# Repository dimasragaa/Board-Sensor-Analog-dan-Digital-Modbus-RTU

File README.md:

# Board-Sensor-Analog-dan-Digital-Modbus-RTU

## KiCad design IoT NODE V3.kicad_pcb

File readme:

# PCB IoT Node - Tugas Akhir

## 📖 Deskripsi Proyek

Repositori ini berisi file desain perangkat keras (Schematic & PCB Layout) dan dokumentasi untuk **IoT Node**. Proyek ini dikembangkan sebagai bagian dari **Tugas Akhir** di Departemen Teknik Elektro, Institut Teknologi Sepuluh Nopember (ITS).

PCB ini dirancang untuk berfungsi sebagai node sensor/aktuator dalam sistem Internet of Things, dengan fokus pada efisiensi daya dan konektivitas yang handal.

## 👤 Penulis

**Dimas Raga**
*   **Institusi:** Teknik Elektro, Institut Teknologi Sepuluh Nopember (ITS)
*   **GitHub:** https://github.com/dimasraga
*   **Instagram:** https://www.instagram.com/dmsragaa

## 📄 Lisensi

Proyek ini dilisensikan di bawah lisensi MIT - lihat file LICENSE untuk detailnya.

---
*Dibuat untuk memenuhi persyaratan Tugas Akhir Teknik Elektro ITS.*

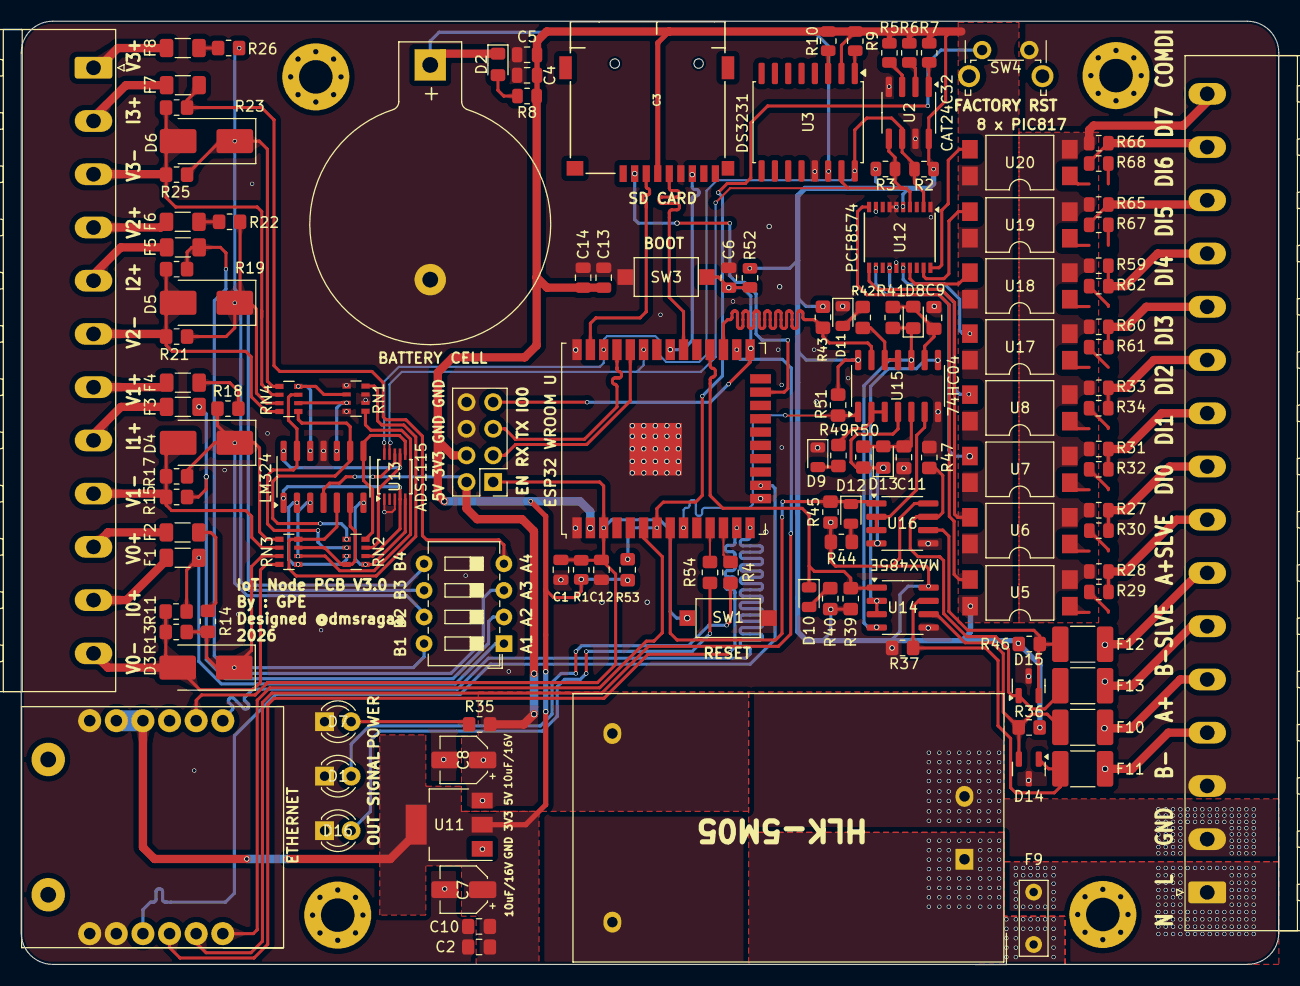
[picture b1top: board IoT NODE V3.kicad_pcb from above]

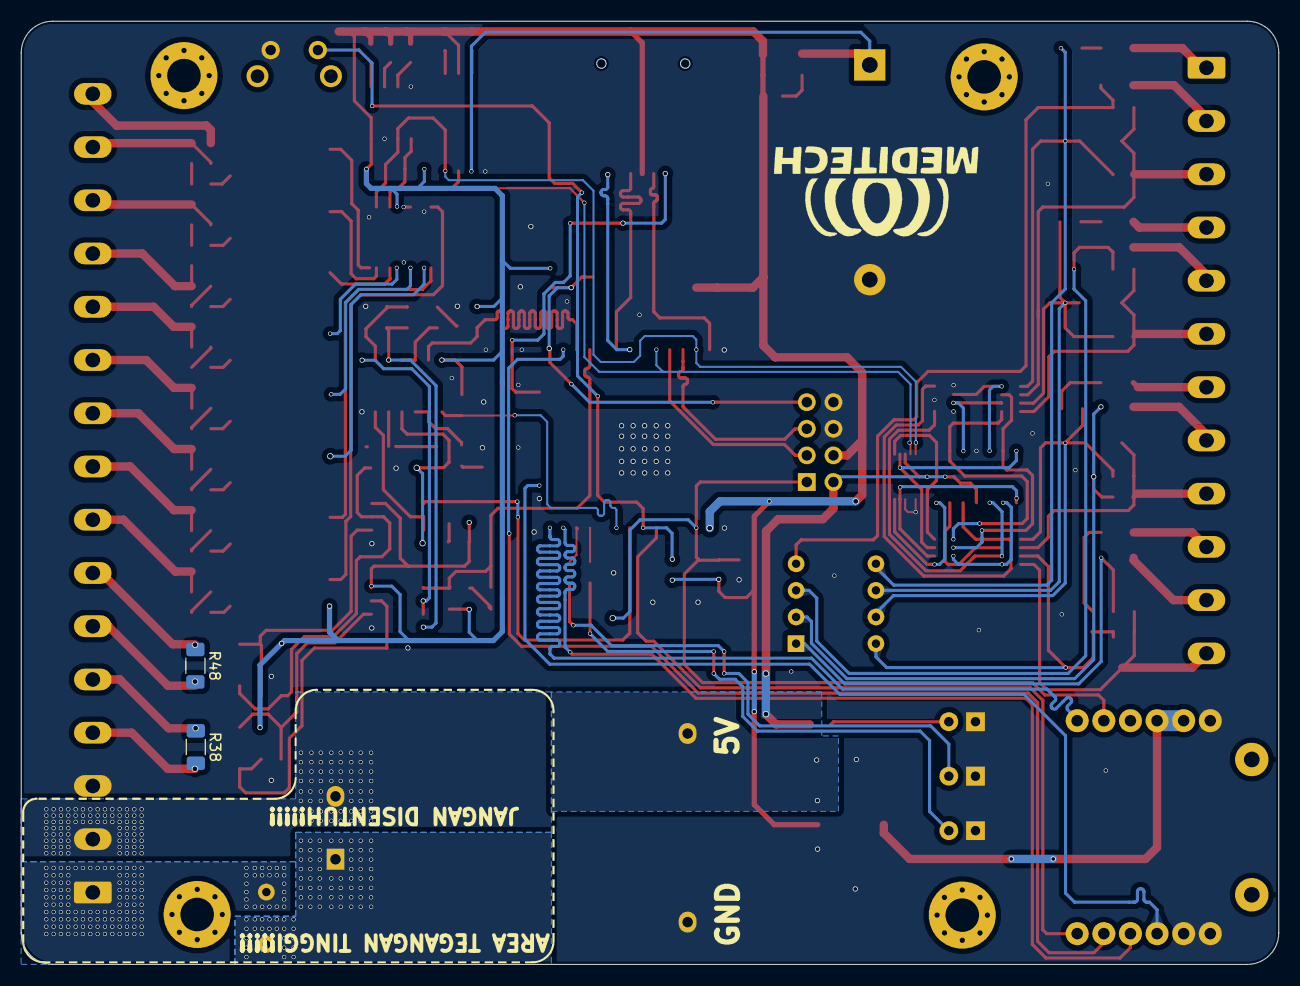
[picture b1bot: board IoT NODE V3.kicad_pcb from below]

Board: 2 copper layers, 120.0 x 90.0 mm, 137 parts (2 on the bottom side), 119 nets.

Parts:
BT1: Battery_Cell; BatteryHolder_Keystone_103_1x20mm
C1, C4, C5, C6, C12: 100nF; C_0805_2012Metric
C2, C10: 100n; C_0805_2012Metric_Pad1.18x1.45mm_HandSolder
C3: L-KLS1-TF-003-H1.85-R; J_SD_Card-micro_socket_A
C7, C8: 10uF/16V; CP_Elec_4x5.8
C9, C11: 33p; C_0805_2012Metric_Pad1.18x1.45mm_HandSolder
C13: 10uF; C_0805_2012Metric
C14: 0.1uF; C_0805_2012Metric
D1, D16: Led Red; LED_D3.0mm
D2, D8, D13: 1N4148; D_0805_2012Metric_Pad1.15x1.40mm_HandSolder
D3, D4, D5, D6: TVS_SMBJ28A; D_SMB_Handsoldering
D7: LED; LED_D3.0mm
D9: TX_Slave; LED_0805_2012Metric
D10: RX; LED_0805_2012Metric
D11: TX; LED_0805_2012Metric
D12: RX_Slave; LED_0805_2012Metric
D14, D15: SM712_SOT23; SOT-23
F1, F2, F3, F4, F5, F6, F7, F8: 150 mA; R_1206_3216Metric_Pad1.30x1.75mm_HandSolder
F9: 1A/250VAC; C_Rect_L7.0mm_W2.5mm_P5.00mm
F10, F11, F12, F13: Fuse_Small; C_1812_4532Metric_Pad1.57x3.40mm_HandSolder
H1, H2, H3, H4: MountingHole; MountingHole_3.2mm_M3_Pad_Via
J1: Screw_Terminal_01x16; PhoenixContact_MSTBA_2,5_16-G-5,08_1x16_P5.08mm_Horizontal
J3: UPLOADER; PinHeader_2x04_P2.54mm_Vertical
J4: Screw_Terminal_01x12; PhoenixContact_MSTBA_2,5_12-G-5,08_1x12_P5.08mm_Horizontal
PS1: HLK-5M05; Converter_ACDC_Hi-Link_HLK-5Mxx
R1, R52: 10K; R_0805_2012Metric
R2, R3, R5, R6, R7, R9, R10: 4.7K; R_0805_2012Metric
R4, R35, R54: 200; R_0805_2012Metric_Pad1.20x1.40mm_HandSolder
R8: 200; R_0805_2012Metric
R11, R15, R19, R23: 100; R_0805_2012Metric_Pad1.20x1.40mm_HandSolder
R13, R14, R17, R18, R21, R22, R25, R26: 510k; R_0805_2012Metric_Pad1.20x1.40mm_HandSolder
R27, R28, R31, R33, R59, R60, R65, R66: 1M; R_0805_2012Metric
R29, R30, R32, R34, R61, R62, R67, R68: 4k3; R_0805_2012Metric
R36, R37, R46, R47: 10k; R_0805_2012Metric_Pad1.20x1.40mm_HandSolder
R38, R48: 120; R_1206_3216Metric_Pad1.30x1.75mm_HandSolder
R39, R43, R45, R51: 4.7k; R_0805_2012Metric_Pad1.20x1.40mm_HandSolder
R40, R42, R44, R49: 2.4k; R_0805_2012Metric_Pad1.20x1.40mm_HandSolder
R41, R50: 56k; R_0805_2012Metric_Pad1.20x1.40mm_HandSolder
R53: 10K; R_0805_2012Metric_Pad1.20x1.40mm_HandSolder
RN1, RN2, RN3, RN4: 10k; R_Array_Convex_4x0603
SW1: RST; SW_SPST_CK_RS282G05A3
SW2: SW_DIP_x04; SW_DIP_SPSTx04_Slide_6.7x11.72mm_W7.62mm_P2.54mm_LowProfile
SW3: BOOT; SW_SPST_CK_RS282G05A3
SW4: FACTORY RST; SW_Tactile_SPST_Angled_PTS645Vx58-2LFS
U1: ESP32-WROOM-32U
U2: CAT24C32WI-G; SOIC-8_3.9x4.9mm_P1.27mm
U3: DS3231SN#; SOIC-16W_7.5x10.3mm_P1.27mm
U4: LM324; SOIC-14_L8.7-W3.9-P1.27-LS6.0-BL
U5, U17: PC817; SMDIP-4_W9.53mm_Clearance8mm
U6, U7, U8, U18, U19, U20: PIC817; SMDIP-4_W9.53mm_Clearance8mm
U9: W5500_V2; W5500
U11: AMS1117-33; SOT-223-3_TabPin2
U12: PCF8574ATS; SSOP-20_4.4x6.5mm_P0.65mm
U13: ADS1115IDGS; TSSOP-10_3x3mm_P0.5mm
U14, U16: MAX485E; SOIC-8_3.9x4.9mm_P1.27mm
U15: 74HC04; SOIC-14_3.9x8.7mm_P1.27mm

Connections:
+3.3V: C2.1, C3.4, C4.1, C5.1, C7.1, C10.1, C13.1, C14.1, J3.4, R1.2, R2.2, R3.2, R5.2, R6.2, R7.2, R8.2, R9.1, R10.1, R36.1, R39.1, R40.1, R43.1, R44.1, R45.1, R46.1, R51.1, R52.2, R53.2, U1.2 (VDD), U2.8 (VCC), U3.2 (VCC), U5.4, U6.4, U7.4, U8.4, U9.10 (3.3V), U9.11 (3.3V), U11.2 (VO), U12.5 (VDD), U14.8 (VCC), U15.14 (VCC), U16.8 (VCC), U17.4, U18.4, U19.4, U20.4
+5V: C8.1, J3.2, PS1.4 (+VO), R35.1, U4.4 (V+), U11.3 (VI), U13.8 (VDD)
/A+: F10.2, J1.5, R38.1
/A+_Slave: F12.2, J1.7, R48.1
/Analog 0: RN2.2 (R2.1), U4.1, U13.4 (AIN0)
/Analog 1: RN2.1 (R1.1), U4.7, U13.5 (AIN1)
/Analog 2: RN2.4 (R4.1), U4.8, U13.6 (AIN2)
/Analog 3: RN2.3 (R3.1), U4.14, U13.7 (AIN3)
/AnalogInput/A01: F1.2, R11.2, SW2.1
/AnalogInput/A02: F3.2, R15.2, SW2.2
/AnalogInput/A03: F5.2, R19.2, SW2.3
/AnalogInput/A04: F7.2, R23.2, SW2.4
/AnalogInput/B01: D3.1 (K), R13.2, R14.1, RN3.7 (R2.2), SW2.8
/AnalogInput/B02: D4.1 (K), R17.2, R18.1, RN3.5 (R4.2), SW2.7
/AnalogInput/B03: D5.1 (K), R21.2, R22.1, RN4.7 (R2.2), SW2.6
/AnalogInput/B04: D6.1 (K), R25.2, R26.1, RN4.5 (R4.2), SW2.5
/B-: F11.2, J1.4, R38.2
/B-_Slave: F13.2, J1.6, R48.2
/COM DI: J1.16, R27.1, R28.1, R31.1, R33.1, R59.1, R60.1, R65.1, R66.1, U5.2, U6.2, U7.2, U8.2, U17.2, U18.2, U19.2, U20.2
/DI0: J1.8, R28.2, R29.1
/DI1: J1.9, R27.2, R30.1
/DI2: J1.10, R31.2, R32.1
/DI3: J1.11, R33.2, R34.1
/DI4: J1.12, R60.2, R61.1
/DI5: J1.13, R59.2, R62.1
/DI6: J1.14, R65.2, R67.1
/DI7: J1.15, R66.2, R68.1
/I0+: F1.1, J4.11
/I1+: F3.1, J4.8
/I2+: F5.1, J4.5
/I3+: F7.1, J4.2
/L: J1.2, PS1.2 (AC(N))
/N: F9.1, J1.1
/RX_Slave: D12.1 (K), R45.2, U1.8 (IO32), U16.1 (RO)
/Rx: D10.1 (K), R39.2, U1.28 (IO17), U14.1 (RO)
/SPI_CLK: U1.13 (IO14), U9.4 (SCLK)
/SPI_MISO: U1.14 (IO12), U9.7 (MISO)
/SPI_MOSI: U1.16 (IO13), U9.3 (MOSI)
/TX_Slave: R51.2, U1.9 (IO33), U15.1
/Tx: R43.2, U1.27 (IO16), U15.13
/V0+: F2.1, J4.10
/V0-: D3.2 (A), J4.12, R11.1, R13.1, RN3.8 (R1.2)
/V1+: F4.1, J4.7
/V1-: D4.2 (A), J4.9, R15.1, R17.1, RN3.6 (R3.2)
/V2+: F6.1, J4.4
/V2-: D5.2 (A), J4.6, R19.1, R21.1, RN4.8 (R1.2)
/V3+: F8.1, J4.1
/V3-: D6.2 (A), J4.3, R23.1, R25.1, RN4.6 (R3.2)
/nINT: U1.6 (IO34), U9.6 (nINT)
/nSS: U1.26 (IO4), U9.5 (nSS)
CLK: C3.5, U1.30 (IO18)
D5_MICRO_SD: C3.2, U1.23 (IO15)
Digital Input 0: U5.3, U12.10 (P0)
Digital Input 1: U6.3, U12.11 (P1)
Digital Input 2: U7.3, U12.12 (P2)
Digital Input 3: U8.3, U12.14 (P3)
Digital Input 4: U12.16 (P4), U17.3
Digital Input 5: U12.17 (P5), U18.3
Digital Input 6: U12.19 (P6), U19.3
Digital Input 7: U12.20 (P7), U20.3
EN: C1.1, C12.1, J3.1, R1.1, SW1.1 (A), U1.3 (EN), U9.8 (nRST)
Earth_Protective: BT1.2 (-), C1.2, C2.2, C3.6, C4.2, C5.2, C6.2, C7.2, C8.2, C9.2, C10.2, C11.2, C12.2, C13.2, C14.2, D1.1 (K), D7.1 (K), D9.1 (K), D11.1 (K), D14.3 (common), D15.3 (common), D16.1 (K), J1.3, J3.6, J3.8, PS1.3 (-VO), R37.2, R47.2, RN1.1 (R1.1), RN1.4 (R4.1), RN1.6 (R3.2), RN1.7 (R2.2), SW1.2 (B), SW3.2 (B), SW4.2 (B), U1.1 (GND), U1.15 (GND), U1.38 (GND), U1.39 (GND), U2.4 (VSS), U2.7 (WP), U3.13 (GND), U4.11 (V-), U9.1 (GND), U9.2 (GND), U9.12 (GND), U11.1 (GND), U12.1 (~INT), U12.6 (A0), U12.7 (A1), U12.9 (A2), U12.15 (VSS), U13.1 (ADDR), U13.3 (GND), U14.5 (GND), U15.7 (GND), U16.5 (GND)
FACTORY: R53.1, SW4.1 (A), U1.7 (IO35)
IO0: C6.1, J3.7, R52.1, SW3.1 (A), U1.25 (IO0)
LED_OUT: R54.2, U1.11 (IO26)
LED_SIG: R4.2, U1.12 (IO27)
MISO: C3.7, U1.31 (IO19)
MOSI: C3.3, U1.37 (IO23)
unnamed: D1.2 (A), R4.1
unnamed: D2.2 (A), R8.1
unnamed: D7.2 (A), R35.2
unnamed: C9.1, D8.2 (A), R41.2, U15.9
unnamed: D8.1 (K), R41.1, U14.4 (DI), U15.10
unnamed: D9.2 (A), R49.2
unnamed: D10.2 (A), R40.2
unnamed: D11.2 (A), R42.2
unnamed: D12.2 (A), R44.2
unnamed: C11.1, D13.2 (A), R50.2, U15.5
unnamed: D13.1 (K), R50.1, U15.4, U16.4 (DI)
unnamed: D14.1 (A1), F11.1, R37.1, U14.7 (B)
unnamed: D14.2 (A2), F10.1, R36.2, U14.6 (A)
unnamed: D15.1 (A1), F13.1, R47.1, U16.7 (B)
unnamed: D15.2 (A2), F12.1, R46.2, U16.6 (A)
unnamed: D16.2 (A), R54.1
unnamed: F2.2, R14.2
unnamed: F4.2, R18.2
unnamed: F6.2, R22.2
unnamed: F8.2, R26.2
unnamed: F9.2, PS1.1 (AC(L))
unnamed: R29.2, U5.1
unnamed: R30.2, U6.1
unnamed: R32.2, U7.1
unnamed: R34.2, U8.1
unnamed: R42.1, U15.11, U15.12
unnamed: R49.1, U15.2, U15.3
unnamed: R61.2, U17.1
unnamed: R62.2, U18.1
unnamed: R67.2, U19.1
unnamed: R68.2, U20.1
unnamed: RN1.8 (R1.2), RN3.4 (R4.1), U4.5 (+)
unnamed: RN1.2 (R2.1), RN4.4 (R4.1), U4.12 (+)
unnamed: RN1.3 (R3.1), RN4.2 (R2.1), U4.10 (+)
unnamed: RN1.5 (R4.2), RN3.2 (R2.1), U4.3 (+)
unnamed: RN2.8 (R1.2), RN3.3 (R3.1), U4.6 (-)
unnamed: RN2.7 (R2.2), RN3.1 (R1.1), U4.2 (-)
unnamed: RN2.6 (R3.2), RN4.3 (R3.1), U4.13 (-)
unnamed: RN2.5 (R4.2), RN4.1 (R1.1), U4.9 (-)
unnamed: R7.1, U2.1 (A0)
unnamed: R6.1, U2.2 (A1)
unnamed: R5.1, U2.3 (A2)
unnamed: R9.2, U3.1 (32KHZ)
unnamed: R10.2, U3.3 (SQW/~INT)
unnamed: U14.2 (~RE), U14.3 (DE), U15.8
unnamed: U15.6, U16.2 (~RE), U16.3 (DE)
RXD: J3.3, U1.34 (RXD0/IO3)
SCL: R2.1, U1.36 (IO22), U2.6 (SCL), U3.16 (SCL), U12.2 (SCL), U13.10 (SCL)
SDA: R3.1, U1.33 (IO21), U2.5 (SDA), U3.15 (SDA), U12.4 (SDA), U13.9 (SDA)
TXD: J3.5, U1.35 (TXD0/IO1)
V_BAT: BT1.1 (+), D2.1 (K), U3.14 (VBAT)

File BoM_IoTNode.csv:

"Reference","Value","Footprint","Qty"
"BT1","Battery_Cell","Battery:BatteryHolder_ComfortableElectronic_CH273-2450_1x2450","1"
"C1,C4,C5,C12","100nF","-- mixed values --","4"
"C2,C10","100n","Capacitor_SMD:C_0805_2012Metric_Pad1.18x1.45mm_HandSolder","2"
"C3","L-KLS1-TF-003-H1.85-R","Connector_Card:J_SD_Card-micro_socket_A","1"
"C7,C8","10uF/16V","Capacitor_SMD:CP_Elec_4x5.8","2"
"C9,C11","33p","Capacitor_SMD:C_0805_2012Metric_Pad1.18x1.45mm_HandSolder","2"
"D1","Led Red","LED_SMD:LED_0805_2012Metric","1"
"D2,D8,D13","1N4148","Diode_THT:D_DO-35_SOD27_P7.62mm_Horizontal","3"
"D3,D4,D5,D6","TVS_SMBJ28A","Diode_SMD:D_SMB_Handsoldering","4"
"D7","LED","LED_SMD:LED_0805_2012Metric","1"
"D9","TX_Slave","LED_SMD:LED_0805_2012Metric","1"
"D10","RX","LED_SMD:LED_0805_2012Metric","1"
"D11","TX","LED_SMD:LED_0805_2012Metric","1"
"D12","RX_Slave","LED_SMD:LED_0805_2012Metric","1"
"D14,D15","SM712_SOT23","Package_TO_SOT_SMD:SOT-23","2"
"F1,F2,F3,F4,F5,F6,F7,F8","150 mA","Resistor_SMD:R_1206_3216Metric_Pad1.30x1.75mm_HandSolder","8"
"F9","1A/250VAC","Capacitor_THT:C_Rect_L7.0mm_W2.5mm_P5.00mm","1"
"F10,F11,F12,F13","Fuse_Small","Fuse:Fuse_1812_4532Metric_Pad1.30x3.40mm_HandSolder","4"
"J2","USB_B_Mini","Connector_USB:USB_Mini-B_Lumberg_2486_01_Horizontal","1"
"J3,J4","Screw_Terminal_01x12","Connector_Phoenix_MSTB:PhoenixContact_MSTBA_2,5_12-G-5,08_1x12_P5.08mm_Horizontal","2"
"PS1","HLK-5M05","IC SOIC:CONV_HLK-5M05","1"
"Q1,Q2","BC817","Package_TO_SOT_SMD:SOT-23","2"
"R1,R54","10K","Resistor_SMD:R_0805_2012Metric","2"
"R2,R3,R5,R6,R7,R9,R10","4.7K","Resistor_SMD:R_0805_2012Metric","7"
"R4,R8,R35","200","-- mixed values --","3"
"R11,R15,R19,R23","240","Resistor_SMD:R_0805_2012Metric_Pad1.20x1.40mm_HandSolder","4"
"R12,R16,R24","10","Resistor_SMD:R_0805_2012Metric_Pad1.20x1.40mm_HandSolder","3"
"R13,R14,R17,R18,R21,R22,R25,R26","510k","Resistor_SMD:R_0805_2012Metric_Pad1.20x1.40mm_HandSolder","8"
"R27,R28,R31,R33,R59,R60,R65,R66","1M","Resistor_SMD:R_0805_2012Metric","8"
"R29,R30,R32,R34,R55,R56,R57,R58,R61,R62,R63,R64,R67,R68,R69,R70","470","Resistor_SMD:R_0805_2012Metric","16"
"R36,R37,R46,R47,R52,R53,RN1,RN2,RN3,RN4","10k","-- mixed values --","10"
"R38,R48","120","Resistor_SMD:R_1206_3216Metric_Pad1.30x1.75mm_HandSolder","2"
"R39,R43,R45,R51","4.7k","Resistor_SMD:R_0805_2012Metric_Pad1.20x1.40mm_HandSolder","4"
"R40,R42,R44,R49","2.4k","Resistor_SMD:R_0805_2012Metric_Pad1.20x1.40mm_HandSolder","4"
"R41,R50","56k","Resistor_SMD:R_0805_2012Metric_Pad1.20x1.40mm_HandSolder","2"
"SW1,SW3","SW_SPST","Button_Switch_SMD:SW_SPST_B3U-1000P","2"
"SW2","SW_DIP_x04","Button_Switch_THT:SW_DIP_SPSTx04_Slide_6.7x11.72mm_W7.62mm_P2.54mm_LowProfile","1"
"U1","ESP32-WROOM-32U","RF_Module:ESP32-WROOM-32U","1"
"U2","CAT24C32WI-G","IC SOIC:SOIC127P600X175-8N","1"
"U3","DS3231SN#","IC SOIC:SOIC127P1032X265-16N","1"
"U4","LM324","IC SOIC:SOIC127P600X175-14N","1"
"U5,U17","PC817","Package_DIP:SMDIP-4_W9.53mm_Clearance8mm","2"
"U6,U7,U8,U18,U19,U20","PIC817","Package_DIP:SMDIP-4_W9.53mm_Clearance8mm","6"
"U9","W5500_V2","TTL to RS485:W5500","1"
"U10","CH340C","Package_SO:SOIC-16_3.9x9.9mm_P1.27mm","1"
"U11","AMS1117-33","Package_TO_SOT_SMD:SOT-223-3_TabPin2","1"
"U12","PCF8574ATS","Package_SO:SSOP-20_4.4x6.5mm_P0.65mm","1"
"U13","ADS1115IDGS","Package_SO:TSSOP-10_3x3mm_P0.5mm","1"
"U14,U16","MAX485E","Package_SO:SOIC-8_3.9x4.9mm_P1.27mm","2"
"U15","74HC04","Package_SO:SOIC-14_3.9x8.7mm_P1.27mm","1"
